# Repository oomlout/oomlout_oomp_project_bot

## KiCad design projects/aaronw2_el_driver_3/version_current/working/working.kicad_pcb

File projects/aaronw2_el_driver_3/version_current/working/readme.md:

# OOMP Project  
##   by   
  
oomp key:   
(snippet of original readme)  
  
- el-driver-3  
EL Wire Driver using Microchip MIC4832  
  
Copyright (C) 2021 Aaron Williams  
  
The enable pin is active high and requires 3V up to VCC.  It is pulled  
low by a 1M resistor.  This board is optimized for 100Hz and 3 square inches  
of EL panel.  
  
VCC is 3-5V  
  
Note that C2 must be rated for 250VDC or higher.  
  
See page 11 of the MIC4832 datasheet at:  
https://ww1.microchip.com/downloads/en/DeviceDoc/MIC4832-Low-Noise-220VPP-EL-Driver-DS20006163A.pdf  
  
  full source readme at [readme_src.md](readme_src.md)  
  
source repo at:   
## Board  

## Schematic  

[schematic pdf](working_schematic.pdf)  
## Images

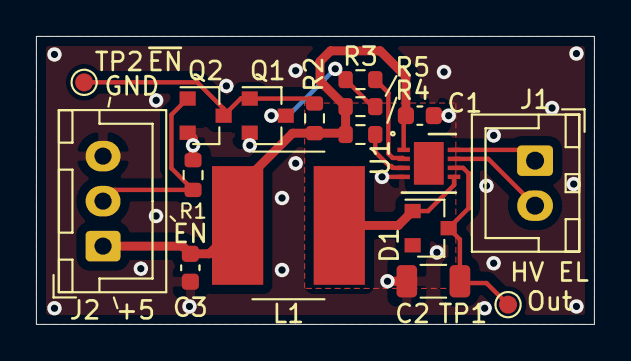
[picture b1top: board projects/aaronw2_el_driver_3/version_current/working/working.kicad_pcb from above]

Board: 2 copper layers, 31.0 x 16.0 mm, 17 parts (0 on the bottom side), 11 nets.

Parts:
C1: 2.2uF; C_0603_1608Metric
C2: 0.015uF 250V; C_1206_3216Metric
C3: 10uF; C_0603_1608Metric
D1: BAS20; SOT-23
J1: Conn_01x02; JST_XH_B2B-XH-A_1x02_P2.50mm_Vertical
J2: Conn_01x03; JST_XH_B3B-XH-A_1x03_P2.50mm_Vertical
L1: 220uH; L_Bourns_SRN8040TA
Q1, Q2: BSS138; SOT-23
R1, R2: 1M; R_0603_1608Metric
R3: 309K; R_0603_1608Metric
R4: 1.69M; R_0603_1608Metric
R5: 1K; R_0603_1608Metric
TP1: TestPoint_Small; TestPoint_Pad_D1.0mm
TP2: TestPoint; TestPoint_Pad_D1.0mm
U1: MIC4832; DFN-8-1EP_3x3mm_P0.5mm_EP1.66x2.38mm

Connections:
+5V: C1.1, C3.1, J2.1, L1.1, R2.2, R4.2, R5.2, U1.1
/CS: C2.1, D1.3, TP1.1, U1.6
/EK_VB: J1.2, U1.7
/EL_VA: J1.1, U1.8
/EN: J2.2, Q2.1, R1.2
/SW: D1.1, L1.2, U1.5
/~EN: Q1.1, Q2.3, R2.1, TP2.1
GND: C1.2, C2.2, C3.2, J2.3, Q1.2, Q2.2, R1.1, U1.4
unnamed: Q1.3, R3.2, R5.1
unnamed: R3.1, U1.2
unnamed: R4.1, U1.3

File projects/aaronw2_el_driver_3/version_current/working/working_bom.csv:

"Id";"Designator";"Footprint";"Quantity";"Designation";"Supplier and ref";
1;"C3";"C_0603_1608Metric";1;"10uF";;;
2;"R5";"R_0603_1608Metric";1;"1K";;;
3;"R2,R1";"R_0603_1608Metric";2;"1M";;;
4;"Q2,Q1";"SOT-23";2;"BSS138";;;
5;"U1";"DFN-8-1EP_3x3mm_P0.5mm_EP1.66x2.38mm";1;"MIC4832";;;
6;"R4";"R_0603_1608Metric";1;"1.69M";;;
7;"R3";"R_0603_1608Metric";1;"309K";;;
8;"L1";"L_Bourns_SRN8040TA";1;"220uH";;;
9;"J2";"JST_XH_B3B-XH-A_1x03_P2.50mm_Vertical";1;"Conn_01x03";;;
10;"J1";"JST_XH_B2B-XH-A_1x02_P2.50mm_Vertical";1;"Conn_01x02";;;
11;"D1";"SOT-23";1;"BAS20";;;
12;"C2";"C_1206_3216Metric";1;"0.015uF 250V";;;
13;"C1";"C_0603_1608Metric";1;"2.2uF";;;

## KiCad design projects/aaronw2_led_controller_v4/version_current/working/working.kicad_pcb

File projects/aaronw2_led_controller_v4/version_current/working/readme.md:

# OOMP Project  
##   by   
  
oomp key:   
(snippet of original readme)  

  full source readme at [readme_src.md](readme_src.md)  
  
source repo at:   
## Board  

## Schematic  

[schematic pdf](working_schematic.pdf)  
## Images

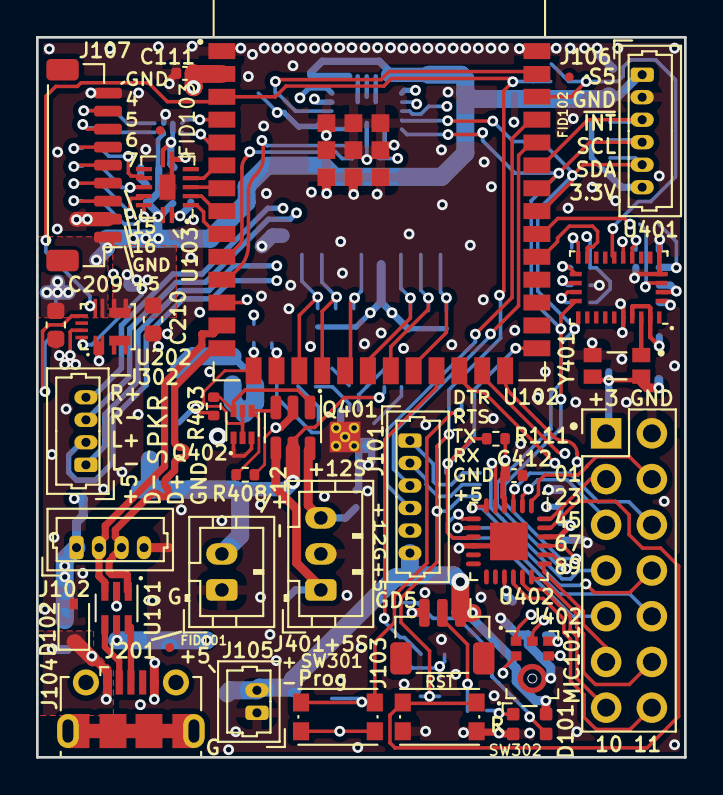
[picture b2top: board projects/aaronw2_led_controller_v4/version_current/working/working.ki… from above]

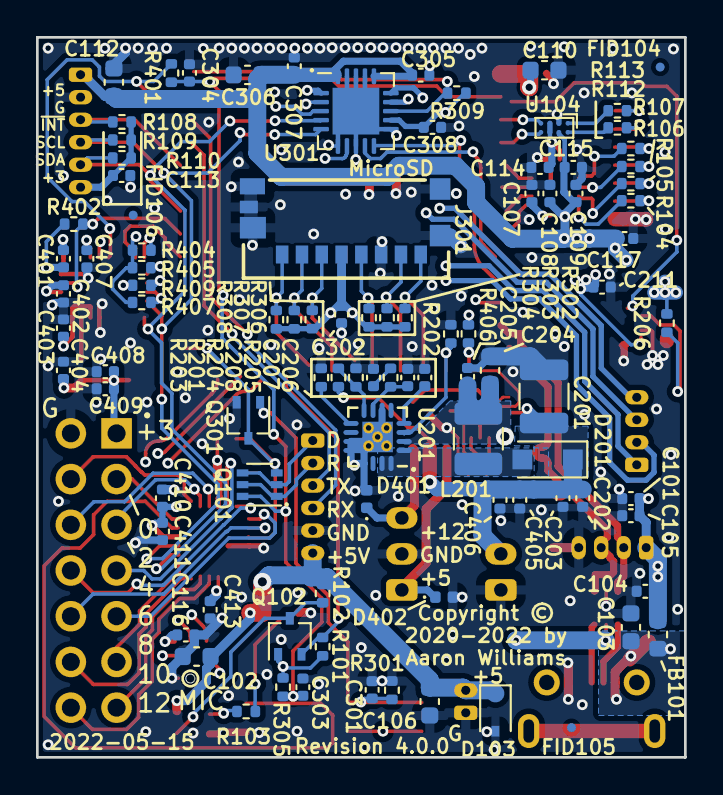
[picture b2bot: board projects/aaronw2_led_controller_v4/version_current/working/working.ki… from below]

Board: 4 copper layers, 36.0 x 40.0 mm, 130 parts (95 on the bottom side), 92 nets.

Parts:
C101, C105, C109, C113, C114, C115, C117, C202, C211, C302, C303, C401, C405, C408, C410: 1uF; C_0402_1005Metric
C102, C103, C106, C112, C306: 10uF; C_0603_1608Metric
C104, C107, C108, C111, C116, C203, C205, C301, C304, C305, C307, C308, C402, C403, C404, C406, C407, C409, C411, C412, C413: 0.1uF; C_0402_1005Metric
C110, C204, C209, C210: 22uF; C_0603_1608Metric
C201: 47uF; C_1210_3225Metric
C206: 22nF; C_0402_1005Metric
C207: 1.5nF; C_0402_1005Metric
C208: 33nF; C_0402_1005Metric
D101: WS2812_2020; LED_WS2812_2020
D102, D103: UDD32C12L01; D_SOD-323
D201: SMD34PL-TP; D_SOD-123F
D401, D402: CDBQR0230R-HF; D_0402_1005Metric
FB101: 2A 300 ohm@100MHz; L_0603_1608Metric
FID101, FID102, FID103, FID104, FID105, FID106: Fiducial; Fiducial_0.5mm_Mask1mm
J101, J106: Molex PicoBlade 6-pin; Molex_PicoBlade_53047-0610_1x06_P1.25mm_Vertical
J102, J302: Molex PicoBlade 4-pin; Molex_PicoBlade_53047-0410_1x04_P1.25mm_Vertical
J103: STATUS OUT; JST_SH_BM03B-SRSS-TB_1x03-1MP_P1.00mm_Vertical
J104: USB_B_Micro; USB_Micro-B_Molex-105017-0001
J105: POWER IN; Molex_PicoBlade_53047-0210_1x02_P1.25mm_Vertical
J107: 5V_LOGIC; JST_SH_BM09B-SRSS-TB_1x09-1MP_P1.00mm_Vertical
J201: 12V_OUT; JST_PH_B2B-PH-K_1x02_P2.00mm_Vertical
J301: Micro_SD_Card; microSD_HC_Molex_047571-0001
J401: Fan PWM; JST_PH_B3B-PH-K_1x03_P2.00mm_Vertical
J402: GPIO_CONN; PinHeader_2x07_P2.54mm_Vertical
L201: 2.2uH; L_1210_3225Metric
MIC101: SPH0645LM4H-B; Knowles_LGA-6_3.5x2.65mm
Q101: UMH3N; SOT-363_SC-70-6
Q102, Q301: BSS138; SOT-323_SC-70
Q401: SIL2301-TP; SOT-23-6
Q402: EM6K7T2R; SOT-563
R101, R102, R108, R404, R405: 4.7K; R_0402_1005Metric
R103, R104, R105, R106, R107, R112, R113: 33; R_0402_1005Metric
R109, R110: 2.2K; R_0402_1005Metric
R111, R202, R204, R206, R301, R302, R303, R304, R305, R306, R307, R308, R309, R401, R402, R403, R406, R407, R408, R409: 10K; R_0402_1005Metric
R201: 86.6K; R_0402_1005Metric
R203: 18.7K; R_0402_1005Metric
R205: 1.54K; R_0402_1005Metric
SW301, SW302: KMR2; SW_Push_1P1T_NO_CK_KMR2
U101: USBUF02W6; SOT-323-6L
U102: ESP32-S3-WROOM-2-N32R8V
U103: NTS0104BQ,115; SOT-762-1
U104: TCA9406ZYPR; Texas_DSBGA-8_0.9x1.9mm_Layout2x4_P0.5mm
U201: TPS55340-Q1; QFN-16-1EP_3x3mm_P0.5mm_EP2.7x2.7mm_ThermalVias
U202: MPM3810GQB-33; Monolithic_QFN-12-2.5x3.0mm_P0.4mm
U301: SSM2518CPZ; LFCSP-20-1EP_4x4mm_P0.5mm_EP2.6x2.6mm
U401: BNO085; LGA-28_5.2x3.8mm_P0.5mm
U402: PCA9575HF; HWQFN-24_EP_4x4_Pitch0.5mm
Y401: OM-7604-C7; OSC_OM-7604-C7

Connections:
+3V3: C107.1, C110.1, C111.1, C113.1, C114.1, C116.1, C210.1, C211.1, C302.1, C308.1, C401.1, C402.1, C403.1, C404.1, C408.1, C409.1, C410.1, C411.1, C412.1, C413.1, J106.6, J301.4 (VDD), J402.1, MIC101.2 (SEL), MIC101.5 (VDD), Q102.1 (G), R101.2, R108.2, R109.2, R110.2, R111.2, R302.2, R303.2, R304.2, R305.1, R306.2, R307.2, R308.2, R309.1, R402.1, R404.2, R405.2, R406.1, R407.1, SW301.1, U101.5 (V3.3), U102.2 (3V3), U103.1 (VCCA), U103.8 (OE), U104.C1 (VCCA), U104.C2 (OE), U202.12 (OUT_S), U202.56 (OUT), U301.3 (ADDR), U301.12 (DVDD), U401.3 (VDD), U401.10 (BL_IND), U401.26 (XOUT32), U401.28 (VDDIO), U402.4 (VDD(IO0)), U402.15 (VDD(IO1)), U402.22 (VDD), Y401.3 (CLKOE), Y401.4 (VDD)
+5V: C101.1, C102.1, C104.1, C105.1, C106.1, C108.1, C109.1, C112.1, C115.1, C117.1, C204.1, C205.1, C209.1, C305.1, C306.1, C307.1, D101.4 (VDD), D103.1 (K), FB101.2, J101.6, J102.1, J103.1, J105.2, J106.1, J107.1, L201.1, Q401.2 (S), R102.2, R206.2, R408.1, U103.14 (VCCB), U104.B2 (VCCB), U201.2 (VIN), U202.7 (VIN), U301.16 (PVDD), U301.20 (PVDD)
+12V: C201.1, C202.1, C203.1, C405.1, C406.1, D201.1 (K), J201.2, Q401.5 (S), R201.1, R403.1
/D+: J104.3 (D+), U101.6 (D4)
/D-: J104.2 (D-), U101.4 (D3)
/DTR: J101.1, Q101.2 (B1), Q101.4 (E2)
/I2S0_BCLK: MIC101.4 (BCLK), U102.26 (STR_3.3_1.8/IO45)
/I2S0_DIN: MIC101.6 (DATA_OUT), U102.25 (IO48)
/I2S0_WSEL: MIC101.1 (WS), U102.24 (IO47)
/IO4: U102.4 (IO4), U104.D1 (SDA_A)
/IO4_H: J107.8, R113.1
/IO5: U102.5 (IO5), U104.D2 (SCL_A)
/IO5_H: J107.7, R112.1
/IO6: U102.6 (IO6), U103.5 (A4)
/IO6_H: J107.6, R107.1
/IO7: U102.7 (IO7), U103.4 (A3)
/IO7_H: J107.5, R106.1
/IO15: U102.8 (IO15), U103.3 (A2)
/IO15_H: J107.4, R105.1
/IO16_H: J107.3, R104.1
/Motion and GPIO/CAP: C407.1, U401.9 (CAP)
/Motion and GPIO/COM2: R407.2, U401.18 (COM2)
/Motion and GPIO/COM3: R409.1, U401.17 (COM3)
/Motion and GPIO/H_SCL: R404.1, U401.15 (H_SCL)
/Motion and GPIO/H_SDA: R405.1, U401.16 (H_SDA)
/Motion and GPIO/P0_0: J402.3, U402.24 (P0_0)
/Motion and GPIO/P0_1: J402.4, U402.1 (P0_1)
/Motion and GPIO/P0_2: J402.5, U402.2 (P0_2)
/Motion and GPIO/P0_3: J402.6, U402.3 (P0_3)
/Motion and GPIO/P0_4: J402.7, U402.5 (P0_4)
/Motion and GPIO/P0_5: J402.8, U402.6 (P0_5)
/Motion and GPIO/P0_6: J402.9, U402.7 (P0_6)
/Motion and GPIO/P0_7: J402.10, U402.8 (P0_7)
/Motion and GPIO/P1_0: J402.11, U402.19 (P1_0)
/Motion and GPIO/P1_1: J402.12, U402.18 (P1_1)
/Motion and GPIO/P1_2: J402.13, U402.17 (P1_2)
/Motion and GPIO/P1_3: J402.14, U402.16 (P1_3)
/Motion and GPIO/SW_5V_IO1: D402.1 (K), J401.1, Q401.4 (D)
/Motion and GPIO/SW_12V: D401.1 (K), J401.3, Q401.6 (D)
/Motion and GPIO/XIN32: U401.27 (XIN32), Y401.1 (CLKOUT)
/Motion and GPIO/~EN_5V: Q401.3 (G), Q402.4 (D), R408.2
/Motion and GPIO/~EN_12V: Q401.1 (G), Q402.6 (D), R403.2
/Power Supplies/COMP: C207.1, R205.2, U201.7 (COMP)
/Power Supplies/EN_5V: R206.1, U202.9 (EN)
/Power Supplies/FB: R201.2, R204.1, U201.8 (FB)
/Power Supplies/FREQ: R203.1, U201.9 (FREQ)
/Power Supplies/SS: C206.1, U201.4 (SS)
/Power Supplies/SW: D201.2 (A), L201.2, U201.1 (SW), U201.15 (SW), U201.16 (SW)
/RTS: J101.2, Q101.1 (E1), Q101.5 (B2)
/RXD0: J101.4, U102.37 (TXD0)
/Reset, Boot, Amp, and SD Card/PGM_IO0_DRV: C301.1, Q301.1 (G), R301.2, SW301.2
/Reset, Boot, Amp, and SD Card/SPKR_L+: J302.2, U301.1 (OUTL+)
/Reset, Boot, Amp, and SD Card/SPKR_L-: J302.1, U301.2 (OUTL-)
/Reset, Boot, Amp, and SD Card/SPKR_R+: J302.4, U301.15 (OUTR+)
/Reset, Boot, Amp, and SD Card/SPKR_R-: J302.3, U301.14 (OUTR-)
/STATUS_LED: Q102.2 (S), R101.1, U102.23 (IO21)
/STS_5V: D101.3 (DIN), Q102.3 (D), R102.1
/STS_DO: J103.2, R103.1
/TXD0: J101.3, U102.36 (RXD0)
/USB_DN: J102.2, U101.3 (D2), U102.13 (USB_DN/IO19)
/USB_DP: J102.3, U101.1 (D1), U102.14 (USB_DP/IO20)
AMP_PWR: R309.2, U102.39 (IO1), U301.13 (~SD)
EN_12V: R202.2, U102.16 (STR_ROM_BOOT/IO46), U201.3 (EN)
FAN_PWM: Q402.2 (G), Q402.5 (G), R406.2, U102.15 (IO3/STR_JTAG_USB)
GND: C101.2, C102.2, C103.2, C104.2, C105.2, C106.2, C107.2, C108.2, C109.2, C110.2, C111.2, C112.2, C113.2, C114.2, C115.2, C116.2, C117.2, C201.2, C202.2, C203.2, C204.2, C205.2, C206.2, C207.2, C208.2, C209.2, C210.2, C211.2, C301.2, C302.2, C303.2, C304.2, C305.2, C306.2, C307.2, C308.2, C401.2, C402.2, C403.2, C404.2, C405.2, C406.2, C407.2, C408.2, C409.2, C410.2, C411.2, C412.2, C413.2, D101.2 (VSS), D102.2 (A), D103.2 (A), D401.2 (A), D402.2 (A), J101.5, J102.4, J103.3, J104.5 (GND), J105.1, J106.2, J107.2, J107.9, J201.1, J301.6 (VSS), J301.9 (SHIELD), J401.2, J402.2, MIC101.3 (GND), Q301.2 (S), Q402.1 (S), Q402.3 (S), R202.1, R203.2, R204.2, R301.1, R409.2, SW302.1, U101.2 (GND), U102.1 (GND), U102.40 (GND), U102.41 (GND), U103.7 (GND), U103.15 (GND), U104.B1 (GND), U201.6 (AGND), U201.11 (PGND), U201.12 (PGND), U201.13 (PGND), U201.17 (AGND), U202.1 (PGND), U202.2 (PGND), U202.11 (AGND), U301.6 (MCLK), U301.8 (GND), U301.11 (SAMOD), U301.17 (GND), U301.18 (GND), U301.19 (GND), U301.21 (GND), U401.2 (GND), U401.5 (PS1), U401.6 (PS0), U401.25 (GNDIO), U402.10 (GND), U402.25 (GND), Y401.2 (GND)
I2S1_BCLK: U102.12 (IO8), U301.7 (BCLK)
I2S1_DOUT: U102.11 (IO18), U301.10 (SDATA)
I2S1_WSEL: U102.10 (IO17), U301.9 (LRCLK)
IO16: U102.9 (IO16), U103.2 (A1)
unnamed: C208.1, R205.1
unnamed: D101.1 (DOUT), R103.2
unnamed: R104.2, U103.13 (B1)
unnamed: R105.2, U103.12 (B2)
unnamed: R106.2, U103.11 (B3)
unnamed: R107.2, U103.10 (B4)
unnamed: R112.2, U104.A2 (SCL_B)
unnamed: R113.2, U104.A1 (SDA_B)
SCL: J106.4, R109.1, U102.34 (IO41), U301.5 (SCL), U401.19 (COM1), U402.21 (SCL)
SDA: J106.5, R110.1, U102.33 (IO40), U301.4 (SDA), U401.20 (COM0), U402.20 (SDA)
SD_CLK: J301.5 (CLK), R304.1, U102.19 (IO11)
SD_CMD: J301.3 (CMD), R306.1, U102.20 (IO12)
SD_D0: J301.7 (DAT0), R303.1, U102.18 (IO10)
SD_D1: J301.8 (DAT1), R302.1, U102.17 (IO9)
SD_D2: J301.1 (DAT2), R308.1, U102.22 (IO14)
SD_D3: J301.2 (DAT3/CD), R307.1, U102.21 (IO13)
VBUS: C103.1, D102.1 (K), FB101.1, J104.1 (VBUS)
~INT2: U102.31 (IO38), U401.14 (~INT)
~INT3: J106.3, R108.1, U102.35 (IO42)
~INT: Q101.3 (C2), Q301.3 (D), R111.1, U102.27 (IO0/STR_SPI_DNLD), U402.9 (~INT)
~M_BOOT_LOAD: R402.2, U102.32 (IO39), U401.4 (~BOOT_LOAD_PIN)
~RESET: C303.1, C304.1, Q101.6 (C1), R305.2, R401.1, SW302.2, U102.3 (EN), U202.8 (PG), U402.23 (~RESET)
~RST_BNO085: R401.2, U102.38 (IO2), U401.11 (~RESET)

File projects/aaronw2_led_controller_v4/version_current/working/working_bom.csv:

"Id";"Designator";"Footprint";"Quantity";"Designation";"Supplier and ref";
1;"FID103,FID101,FID102,FID104,FID106,FID105";"Fiducial_0.5mm_Mask1mm";6;"Fiducial";;;
2;"U401";"LGA-28_5.2x3.8mm_P0.5mm";1;"BNO085";;;
3;"J104";"USB_Micro-B_Molex-105017-0001";1;"USB_B_Micro";;;
4;"C111,C412,C205,C403,C308,C409,C305,C301,C108,C402,C406,C304,C116,C411,C203,C407,C404,C413,C307,C107,C104";"C_0402_1005Metric";21;"0.1uF";;;
5;"U101";"SOT-323-6L";1;"USBUF02W6";;;
6;"D102,D103";"D_SOD-323";2;"UDD32C12L01";;;
7;"U402";"HWQFN-24_EP_4x4_Pitch0.5mm";1;"PCA9575HF";;;
8;"SW302,SW301";"SW_Push_1P1T_NO_CK_KMR2";2;"KMR2";;;
9;"J101,J106";"Molex_PicoBlade_53047-0610_1x06_P1.25mm_Vertical";2;"Molex PicoBlade 6-pin";;;
10;"J107";"JST_SH_BM09B-SRSS-TB_1x09-1MP_P1.00mm_Vertical";1;"5V_LOGIC";;;
11;"R408,R111,R403,R307,R305,R202,R206,R409,R401,R301,R308,R407,R303,R402,R302,R204,R406,R304,R306,R309";"R_0402_1005Metric";20;"10K";;;
12;"MIC101";"Knowles_LGA-6_3.5x2.65mm";1;"SPH0645LM4H-B";;;
13;"J105";"Molex_PicoBlade_53047-0210_1x02_P1.25mm_Vertical";1;"POWER IN";;;
14;"J402";"PinHeader_2x07_P2.54mm_Vertical";1;"GPIO_CONN";;;
15;"Q402";"SOT-563";1;"EM6K7T2R";;;
16;"U102";"ESP32-S3-WROOM-2-N32R8V";1;"ESP32-S3-WROOM-2-N32R8V";;;
17;"U202";"Monolithic_QFN-12-2.5x3.0mm_P0.4mm";1;"MPM3810GQB-33";;;
18;"J103";"JST_SH_BM03B-SRSS-TB_1x03-1MP_P1.00mm_Vertical";1;"STATUS OUT";;;
19;"Q401";"SOT-23-6";1;"SIL2301-TP";;;
20;"C210,C209,C204,C110";"C_0603_1608Metric";4;"22uF";;;
21;"J201";"JST_PH_B2B-PH-K_1x02_P2.00mm_Vertical";1;"12V_OUT";;;
22;"J102,J302";"Molex_PicoBlade_53047-0410_1x04_P1.25mm_Vertical";2;"Molex PicoBlade 4-pin";;;
23;"U103";"SOT-762-1";1;"NTS0104BQ,115";;;
24;"D101";"LED_WS2812_2020";1;"WS2812_2020";;;
25;"J401";"JST_PH_B3B-PH-K_1x03_P2.00mm_Vertical";1;"Fan PWM";;;
26;"Y401";"OSC_OM-7604-C7";1;"OM-7604-C7";;;
27;"C103,C102,C306,C112,C106";"C_0603_1608Metric";5;"10uF";;;
28;"C207";"C_0402_1005Metric";1;"1.5nF";;;
29;"C408,C302,C113,C410,C114,C401,C117,C115,C105,C303,C405,C211,C101,C202,C109";"C_0402_1005Metric";15;"1uF";;;
30;"R103,R113,R112,R107,R106,R104,R105";"R_0402_1005Metric";7;"33";;;
31;"D201";"D_SOD-123F";1;"SMD34PL-TP";;;
32;"R405,R102,R101,R404,R108";"R_0402_1005Metric";5;"4.7K";;;
33;"D402,D401";"D_0402_1005Metric";2;"CDBQR0230R-HF";;;
34;"R109,R110";"R_0402_1005Metric";2;"2.2K";;;
35;"R203";"R_0402_1005Metric";1;"18.7K";;;
36;"C206";"C_0402_1005Metric";1;"22nF";;;
37;"U104";"Texas_DSBGA-8_0.9x1.9mm_Layout2x4_P0.5mm";1;"TCA9406ZYPR";;;
38;"U201";"QFN-16-1EP_3x3mm_P0.5mm_EP2.7x2.7mm_ThermalVias";1;"TPS55340-Q1";;;
39;"Q301,Q102";"SOT-323_SC-70";2;"BSS138";;;
40;"C201";"C_1210_3225Metric";1;"47uF";;;
41;"Q101";"SOT-363_SC-70-6";1;"UMH3N";;;
42;"C208";"C_0402_1005Metric";1;"33nF";;;
43;"R205";"R_0402_1005Metric";1;"1.54K";;;
44;"R201";"R_0402_1005Metric";1;"86.6K";;;
45;"J301";"microSD_HC_Molex_047571-0001";1;"Micro_SD_Card";;;
46;"L201";"L_1210_3225Metric";1;"2.2uH";;;
47;"U301";"LFCSP-20-1EP_4x4mm_P0.5mm_EP2.6x2.6mm";1;"SSM2518CPZ";;;
48;"FB101";"L_0603_1608Metric";1;"2A 300 ohm@100MHz";;;

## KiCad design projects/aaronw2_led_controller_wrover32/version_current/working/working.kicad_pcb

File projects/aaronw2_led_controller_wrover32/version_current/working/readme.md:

# OOMP Project  
##   by   
  
oomp key:   
(snippet of original readme)  
  
- led-controller-wrover32  
Wrover32 based LED controller for NeoPixels and DotStars with 5v signalling  
and micro SD  
  
Power:  
  
This board is powered by 5V and generates a 3.3V supply via U1.  This board  
may draw up to 500ma of current at 5V.  The 3.3V supply is capable of  
generating up to 1A.  
  
This board makes use of a Torex Semiconductor XCL220 micro DC/DC converter  
to efficiently provide 3.3v of power.  This inexpensive device is reportedly  
93% efficient which should increase battery life and reduce heat buildup.  
  
Do not draw more than 500ma from any single power or ground pin on J2 or J4.  
  
On J5, VBUS is 5V as are pins 9 and 12 on J4 and pin 1 on J2.  
J6 and J7 also provide +5V at the + terminal.  
  
5V may be shunted through the board, but limit the current to no more than 2A.  
  
5V may be supplied by any pin, however power provided by the micro SD  
connector J3 should be limited to 500 ma.  
  
USB:  
  
There are two USB connectors on the board for programming.  The Micro USB  
connector J3 or J5 may be used.  Do not use both connectors.  J5 is designed  
so either a 4 pin header or a USB cable can be soldered to the board,  
eliminating the need to use micro USB.  
  
The USB port is connected to a SI Labs CP2102 USB to serial UART for  
programming and debugging purposes.  
  
I/O:  
  
Unlike most if not all other ESP32 based boards, this board includes a  
3V to 5V bidirectional level shifter for IO25, IO26, IO32 and IO33.  These  
I/O ports can also be driven by the RTC in the ESP32 to help offload driving  
  full source readme at [readme_src.md](readme_src.md)  
  
source repo at:   
## Board  

## Schematic  

[schematic pdf](working_schematic.pdf)  
## Images

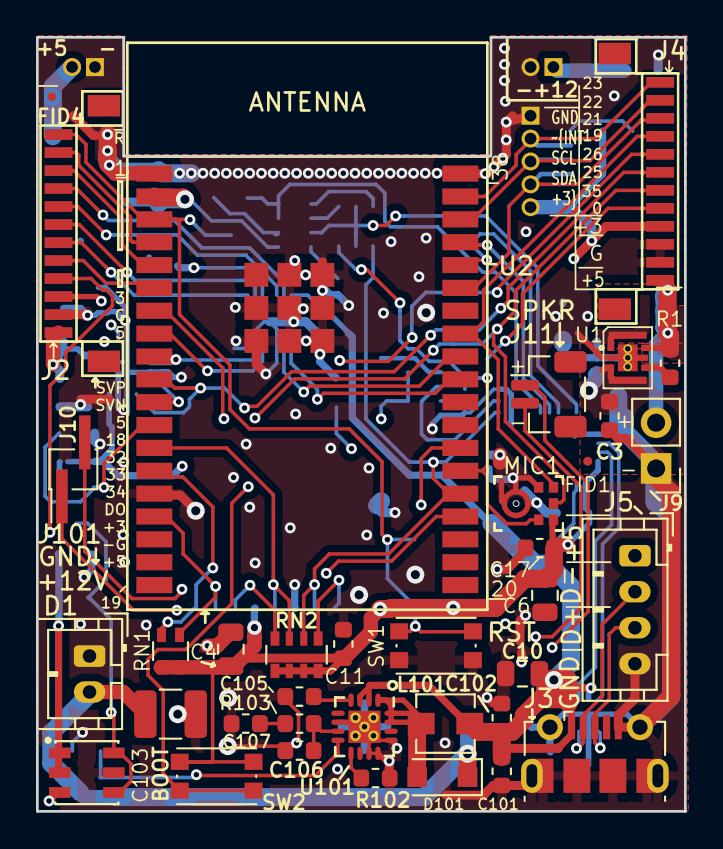
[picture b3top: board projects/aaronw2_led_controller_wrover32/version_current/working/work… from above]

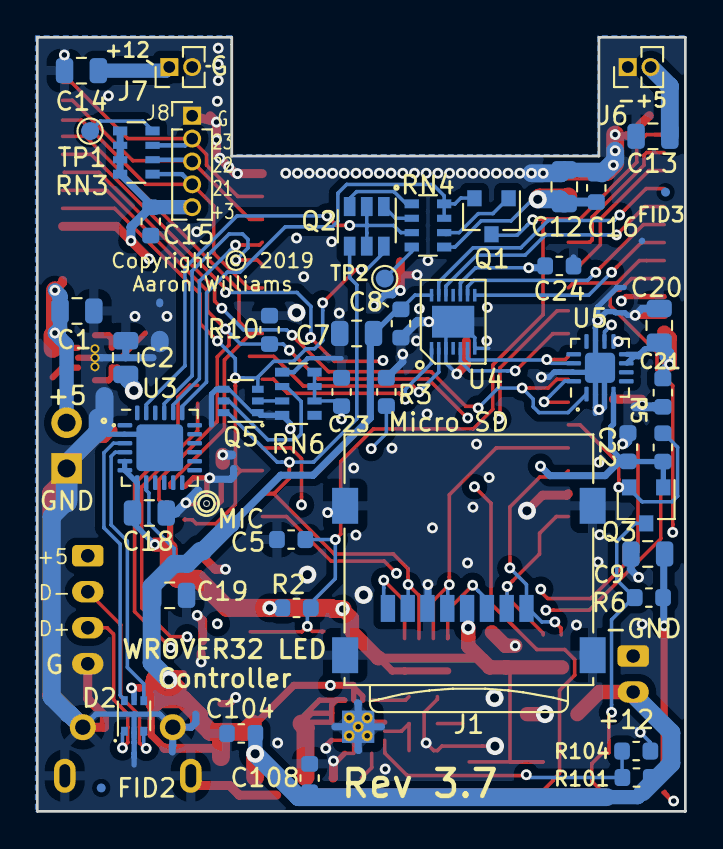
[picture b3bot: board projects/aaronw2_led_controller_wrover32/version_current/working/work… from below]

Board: 4 copper layers, 36.0 x 43.0 mm, 82 parts (46 on the bottom side), 59 nets.

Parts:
C1, C2, C4, C6, C7, C9, C10, C13, C14, C18, C19, C20: 10uF; C_0805_2012Metric
C3, C11, C15, C104: 1uF; C_0603_1608Metric
C5, C8, C16, C17, C21, C22, C24, C102, C108: 0.1uF; C_0603_1608Metric
C12: 22uF; C_0805_2012Metric
C23, C105: 22nF; C_0603_1608Metric
C101: 22uF; C_0603_1608Metric
C103: 47uF; C_1210_3225Metric
C106: 820pF; C_0603_1608Metric
C107: 47nF; C_0603_1608Metric
D1: WS2813-MINI; LED_WS2813-MINI-2
D2: USBLC6-2P6; SOT-666
D101: D_Schottky; D_SOD-123F
FID1, FID2, FID3, FID4: DNF; Fiducial_0.5mm_Mask1mm
J1: Micro_SD_Card; microSD_HC_Wuerth_693072010801
J2, J4: BM12B-SRSS-TBT(LF)(SN); BM12B-SRSS-TB
J3: USB_B_Micro; USB_Micro-B_Molex-105017-0001
J5: Conn_01x04; JST_PH_B4B-PH-K_1x04_P2.00mm_Vertical
J6, J7: Conn_01x02 DNF; PinHeader_1x02_P1.27mm_Vertical
J8: Conn_01x05 DNF; PinHeader_1x05_P1.27mm_Vertical
J9: Conn_01x02 DNF; PinHeader_1x02_P2.54mm_Vertical
J10: Conn_01x02 DNF; PinHeader_1x02_P1.27mm_Vertical_SMD_Pin1Left
J11: Conn_01x02; JST_SH_BM02B-SRSS-TB_1x02-1MP_P1.00mm_Vertical
J101: Conn_01x02; JST_PH_B2B-PH-K_1x02_P2.00mm_Vertical
L101: 3.3uH; L_Vishay_IHLP-1212
MIC1: SPH0645LM4H-B
Q1: MMSS8050-H-TP; SOT-23
Q2: FMB2222A; SOT-23-6
Q3: BSS138; SOT-23
Q5: BSS138DW-7-F; SOT-363_SC-70-6
R1, R3, R104: 10K; R_0603_1608Metric
R2: 470; R_0603_1608Metric
R5, R6: 4.7K; R_0603_1608Metric
R10: 100K; R_0603_1608Metric
R101: 86.6K; R_0603_1608Metric
R102: 18.7K; R_0603_1608Metric
R103: 1.62K; R_0603_1608Metric
RN1: 10K; R_Array_Convex_2x0603
RN2: 10K; R_Array_Convex_4x0603
RN3: 4.7K; R_Array_Convex_4x0603
RN4, RN6: 100K; R_Array_Convex_4x0603
SW1, SW2: SW_SPST_KMR2
TP1, TP2: DNF; TestPoint_Pad_D1.0mm
U1: XCL220; CL-2025-02
U2: ESP32-WROVER; ESP32-WROOVER
U3: CP2104; QFN-24-1EP_4x4mm_P0.5mm_EP2.6x2.6mm
U4: MAX3379EETD; TDFN-14_3x3mm_P0.4mm_EP1.78x2.35mm
U5: MAX98357A; VQFN-16-1EP_3x3mm_P0.5mm_EP1.68x1.68mm
U101: TPS55340-Q1; QFN-16-1EP_3x3mm_P0.5mm_EP2.7x2.7mm_ThermalVias

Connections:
+3V3: C2.1, C3.1, C4.1, C6.1, C11.1, C12.1, C15.1, C16.1, C17.1, C18.1, C22.1, C24.1, J1.4, J2.3, J4.9, J8.5, MIC1.5, Q3.1, R2.1, R5.2, RN1.1, RN1.2, RN2.1, RN2.2, RN2.3, RN2.4, RN3.5, RN3.6, RN3.7, RN3.8, RN4.5, SW2.1, U1.3, U1.8, U2.2, U3.5, U3.6, U3.7, U4.10, U5.4
+12V: C14.1, C103.1, C104.1, C108.1, D101.1, J7.1, J101.2, R101.1
/12v-booster/COMP: C106.1, R103.2, U101.7
/12v-booster/FB: R101.2, R104.1, U101.8
/12v-booster/FREQ: R102.1, U101.9
/12v-booster/SS: C105.1, U101.4
/12v-booster/SW: D101.2, L101.2, U101.1, U101.15, U101.16
/Amp/SPKR+: J10.1, J11.1, U5.9
/Amp/SPKR-: J10.2, J11.2, U5.10
/D+: D2.1, J3.3, J5.3
/D-: D2.3, J3.2, J5.2
/DO: D1.3, J2.4
/DTR: Q2.2, Q2.5, RN4.3, U3.23
/IO0_RTS_DRV: Q2.1, RN4.2
/IO2_RTS_DRV: Q2.3, RN4.1
/IO4: J1.8, RN2.5, U2.26
/IO12: J1.1, RN1.4, U2.14
/IO13: J1.2, RN1.3, U2.16
/IO14: J1.5, RN2.7, U2.13
/IO15: J1.3, RN2.8, U2.23
/IO19: J4.4, MIC1.1, U2.31
/IO21: J4.3, J8.4, RN3.1, U2.33
/IO22: J4.2, J8.3, RN3.2, U2.36
/IO23: J4.1, J8.2, RN3.3, U2.37
/IO27: Q3.2, R5.1, U2.12
/IO27_5V: D1.4, D1.6, Q3.3, R6.1
/IO34: J2.5, U2.6
/IO35: J4.7, MIC1.6, R10.2, U2.7
/RST_DTR_DRV: Q1.1, RN4.6
/RTS: Q1.2, RN4.7, RN4.8, U3.19
/RXD0: U2.34, U3.21
/Reset_Boot/PGM_IO0_DRV: Q5.5, RN6.6
/Reset_Boot/PGM_IO2_DRV: Q5.2, RN6.7
/Reset_Boot/~PGM_SW_OUT: C23.1, R3.1, RN6.2, RN6.3, RN6.4, SW2.2
/SENSOR_VN: J2.10, U2.5
/SENSOR_VP: J2.11, U2.4
/TXD0: U2.35, U3.20
/USB_D+: D2.6, U3.3
/USB_D-: D2.4, U3.4
GND: C1.2, C2.2, C3.2, C4.2, C5.2, C6.2, C7.2, C8.2, C9.2, C10.2, C11.2, C12.2, C13.2, C14.2, C15.2, C16.2, C17.2, C18.2, C19.2, C20.2, C21.2, C22.2, C23.2, C24.2, C101.2, C102.2, C103.2, C104.2, C105.2, C106.2, C107.2, C108.2, D1.5, D2.2, J1.6, J1.9, J2.2, J3.5, J3.6, J4.10, J4.11, J5.4, J6.1, J7.2, J8.1, J9.1, J101.1, MIC1.2, MIC1.3, Q5.1, Q5.4, R3.2, R10.1, R102.2, R104.2, RN6.5, RN6.8, SW1.1, U1.2, U1.5, U1.9, U2.1, U2.15, U2.38, U2.39, U3.2, U3.25, U4.3, U4.7, U4.15, U5.2, U5.3, U5.11, U5.15, U5.17, U101.6, U101.11, U101.12, U101.13, U101.17
IO0: J4.8, MIC1.4, Q2.6, Q5.3, U2.25
IO2: J1.7, Q2.4, Q5.6, RN2.6, U2.24
IO5: U2.29, U4.1
IO5_H: J2.9, U4.13
IO18: U2.30, U4.2
IO18_H: J2.8, U4.12
IO25: J4.6, U2.10, U5.1
IO26: J4.5, U2.11, U5.16
IO32: U2.8, U4.5
IO32_H: J2.7, U4.9
IO33: U2.9, U4.6, U5.14
IO33_H: J2.6, U4.8
unnamed: C107.1, R103.1
unnamed: R1.1, U1.4
unnamed: RN3.4, TP1.1
unnamed: RN4.4, TP2.1
unnamed: U1.1, U1.7
VBUS: C1.1, C7.1, C8.1, C9.1, C10.1, C13.1, C19.1, C20.1, C21.1, C101.1, C102.1, D1.1, D1.2, D2.5, J2.1, J3.1, J4.12, J5.1, J6.2, J9.2, L101.1, R1.2, R6.2, U1.6, U3.8, U4.14, U5.7, U5.8, U101.2, U101.3
~RESET: C5.1, J2.12, Q1.3, R2.2, SW1.2, U2.3

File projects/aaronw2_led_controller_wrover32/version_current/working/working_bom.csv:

"Id";"Designator";"Footprint";"Quantity";"Designation";"Supplier and ref";
1;"C18,C7,C20,C19,C6,C2,C9,C10,C13,C14,C1,C4";"C_0805_2012Metric";12;"10uF";;;
2;"U3";"QFN-24-1EP_4x4mm_P0.5mm_EP2.6x2.6mm";1;"CP2104";;;
3;"D1";"LED_WS2813-MINI-2";1;"WS2813-MINI";;;
4;"Q2";"SOT-23-6";1;"FMB2222A";;;
5;"U2";"ESP32-WROOVER";1;"ESP32-WROVER";;;
6;"U4";"TDFN-14_3x3mm_P0.4mm_EP1.78x2.35mm";1;"MAX3379EETD";;;
7;"C24,C8,C5,C22,C21,C108,C102,C17,C16";"C_0603_1608Metric";9;"0.1uF";;;
8;"J10";"PinHeader_1x02_P1.27mm_Vertical_SMD_Pin1Left";1;"Conn_01x02 DNF";;;
9;"J7,J6";"PinHeader_1x02_P1.27mm_Vertical";2;"Conn_01x02 DNF";;;
10;"MIC1";"SPH0645LM4H-B";1;"SPH0645LM4H-B";;;
11;"R3,R104,R1";"R_0603_1608Metric";3;"10K";;;
12;"SW1,SW2";"SW_SPST_KMR2";2;"SW_SPST_KMR2";;;
13;"Q5";"SOT-363_SC-70-6";1;"BSS138DW-7-F";;;
14;"U5";"VQFN-16-1EP_3x3mm_P0.5mm_EP1.68x1.68mm";1;"MAX98357A";;;
15;"Q1";"SOT-23";1;"MMSS8050-H-TP";;;
16;"R2";"R_0603_1608Metric";1;"470";;;
17;"RN6,RN4";"R_Array_Convex_4x0603";2;"100K";;;
18;"C23,C105";"C_0603_1608Metric";2;"22nF";;;
19;"J11";"JST_SH_BM02B-SRSS-TB_1x02-1MP_P1.00mm_Vertical";1;"Conn_01x02";;;
20;"FID4,FID3,FID2,FID1";"Fiducial_0.5mm_Mask1mm";4;"DNF";;;
21;"J9";"PinHeader_1x02_P2.54mm_Vertical";1;"Conn_01x02 DNF";;;
22;"J5";"JST_PH_B4B-PH-K_1x04_P2.00mm_Vertical";1;"Conn_01x04";;;
23;"J101";"JST_PH_B2B-PH-K_1x02_P2.00mm_Vertical";1;"Conn_01x02";;;
24;"J1";"microSD_HC_Wuerth_693072010801";1;"Micro_SD_Card";;;
25;"L101";"L_Vishay_IHLP-1212";1;"3.3uH";;;
26;"U101";"QFN-16-1EP_3x3mm_P0.5mm_EP2.7x2.7mm_ThermalVias";1;"TPS55340-Q1";;;
27;"C101";"C_0603_1608Metric";1;"22uF";;;
28;"C104,C15,C3,C11";"C_0603_1608Metric";4;"1uF";;;
29;"C106";"C_0603_1608Metric";1;"820pF";;;
30;"C107";"C_0603_1608Metric";1;"47nF";;;
31;"C103";"C_1210_3225Metric";1;"47uF";;;
32;"D101";"D_SOD-123F";1;"D_Schottky";;;
33;"R101";"R_0603_1608Metric";1;"86.6K";;;
34;"R102";"R_0603_1608Metric";1;"18.7K";;;
35;"R103";"R_0603_1608Metric";1;"1.62K";;;
36;"J8";"PinHeader_1x05_P1.27mm_Vertical";1;"Conn_01x05 DNF";;;
37;"RN3";"R_Array_Convex_4x0603";1;"4.7K";;;
38;"J3";"USB_Micro-B_Molex-105017-0001";1;"USB_B_Micro";;;
39;"Q3";"SOT-23";1;"BSS138";;;
40;"D2";"SOT-666";1;"USBLC6-2P6";;;
41;"J4,J2";"BM12B-SRSS-TB";2;"BM12B-SRSS-TBT(LF)(SN)";;;
42;"RN1";"R_Array_Convex_2x0603";1;"10K";;;
43;"RN2";"R_Array_Convex_4x0603";1;"10K";;;
44;"R5,R6";"R_0603_1608Metric";2;"4.7K";;;
45;"R10";"R_0603_1608Metric";1;"100K";;;
46;"C12";"C_0805_2012Metric";1;"22uF";;;
47;"U1";"CL-2025-02";1;"XCL220";;;

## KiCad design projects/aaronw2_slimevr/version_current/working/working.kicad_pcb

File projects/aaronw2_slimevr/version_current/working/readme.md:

# OOMP Project  
##   by   
  
(snippet of original readme)  

  full source readme at [readme_src.md](readme_src.md)  
  
source repo at:   
## Board  

## Schematic  

[schematic pdf](working_schematic.pdf)  
## Images

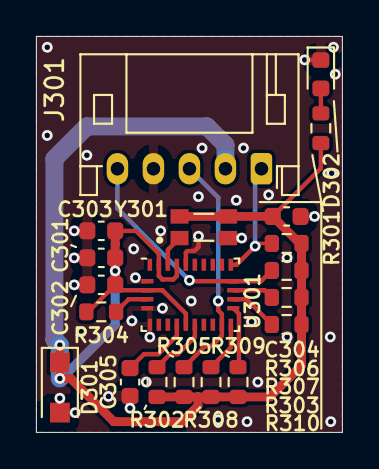
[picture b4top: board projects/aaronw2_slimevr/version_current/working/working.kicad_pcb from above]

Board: 2 copper layers, 17.0 x 22.0 mm, 20 parts (0 on the bottom side), 14 nets.

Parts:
C301: 10uF 10V; C_0603_1608Metric
C302, C303, C304, C305: 0.1uF; C_0603_1608Metric
D301: DSS12UTR; D_SOD-123F
D302: Green; LED_0603_1608Metric
J301: External Motion; JST_PH_S5B-PH-K_1x05_P2.00mm_Horizontal
R301: 330; R_0603_1608Metric
R302, R303, R304, R305, R310: 10K; R_0603_1608Metric
R306, R307, R308, R309: 2.2K; R_0603_1608Metric
U301: BNO085; LGA-28_5.2x3.8mm_P0.5mm
Y301: OM-7604-C7; OSC_OM-7604-C7

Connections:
+3V3: C301.1, C302.1, C303.1, C304.1, D301.1 (K), J301.2, R301.2, R302.1, R303.1, R304.1, R305.1, R306.1, R307.1, R308.1, R309.1, R310.1, U301.3 (VDD), U301.10 (BL_IND), U301.26 (XOUT32), U301.28 (VDDIO), Y301.3 (CLKOE), Y301.4 (VDD)
/B_CLK: U301.27 (XIN32), Y301.1 (CLKOUT)
/CAP: C305.1, U301.9 (CAP)
/SCL: J301.5, R307.2, U301.19 (COM1)
/SDA: J301.1, R306.2, U301.20 (COM0)
/~BNO_BOOT: R304.2, U301.4 (~BOOT_LOAD_PIN)
/~BNO_RESET: R302.2, U301.11 (~RESET)
/~INT1: J301.3, R305.2, U301.14 (INT)
GND: C301.2, C302.2, C303.2, C304.2, C305.2, D301.2 (A), D302.1 (K), J301.4, U301.2 (GND), U301.5 (PS1), U301.6 (PS0), U301.25 (GNDIO), Y301.2 (GND)
unnamed: D302.2 (A), R301.1
unnamed: R303.2, U301.18 (COM2)
unnamed: R308.2, U301.15 (H_SCL)
unnamed: R309.2, U301.16 (H_SDA)
unnamed: R310.2, U301.17 (COM3)

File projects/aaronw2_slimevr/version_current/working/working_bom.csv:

"Id";"Designator";"Footprint";"Quantity";"Designation";"Supplier and ref";
1;"R301";"R_0603_1608Metric";1;"330";;;
2;"C303,C304,C302,C305";"C_0603_1608Metric";4;"0.1uF";;;
3;"U301";"LGA-28_5.2x3.8mm_P0.5mm";1;"BNO085";;;
4;"J301";"JST_PH_S5B-PH-K_1x05_P2.00mm_Horizontal";1;"External Motion";;;
5;"R303,R304,R305,R302,R310";"R_0603_1608Metric";5;"10K";;;
6;"D302";"LED_0603_1608Metric";1;"Green";;;
7;"R306,R309,R307,R308";"R_0603_1608Metric";4;"2.2K";;;
8;"D301";"D_SOD-123F";1;"DSS12UTR";;;
9;"C301";"C_0603_1608Metric";1;"10uF 10V";;;
10;"Y301";"OSC_OM-7604-C7";1;"OM-7604-C7";;;

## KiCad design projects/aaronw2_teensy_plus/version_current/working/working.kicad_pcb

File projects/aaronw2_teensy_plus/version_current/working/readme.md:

# OOMP Project  
##   by   
  
oomp key:   
(snippet of original readme)  
  
Teensy Plus  
Revision 3.3  
  
Copyright (C) 2019 by Aaron Williams  
  
This board is designed to be mounted to a PJRC Teensy 4.0 and 3.2 board.  
It brings out the I/Os of the Teensy and provides a 3V to 5V level shifter  
and a WS2813mini NeoPixel in order to drive up to four channels of  
NeoPixels.  The 5V channels should be compatible with the FastLED library  
for the Teensy 4.0 (not 3.2).  In addition, this board provides a switchable  
12V, 500ma output for driving a fan or other 12V accessories.  Note that  
while the boost circuit is fairly efficient that it will draw around 2.75 times  
as much current at 5V as the 12V output, so at 500ma it could potentially  
draw around 1.4 amps.  If the 12V is not needed then it does not need to be  
stuffed.  
  
This board is designed to be mounted back-to-back with the Teensy 3.2 or  
4.0 board. Note that the extra pins on the back will not be accessible  
once this board is soldered in place.  It can be connected by soldering  
board headers or using headers and sockets.  
  
Not all of the pins are used and not all need to be hooked up.  
  
On/OFF, Program and VBat are not hooked up.  Additionally J9 does not  
need to be connected and can be used for an additional 5V pin.  
  
IO0, IO1, IO2 and IO3 are passed to the level shifter and IO23 is  
connected to the enable pin of the level shifter.  IO3 then goes to  
the WS2813mini.  
  
3.3V is obtained from the Teensy board which cannot supply a lot of  
current.  Please do not exceed 100ma.  
  
J8 brings provides 3.3V, ground and IO4   
  full source readme at [readme_src.md](readme_src.md)  
  
source repo at:   
## Board  

## Schematic  

[schematic pdf](working_schematic.pdf)  
## Images

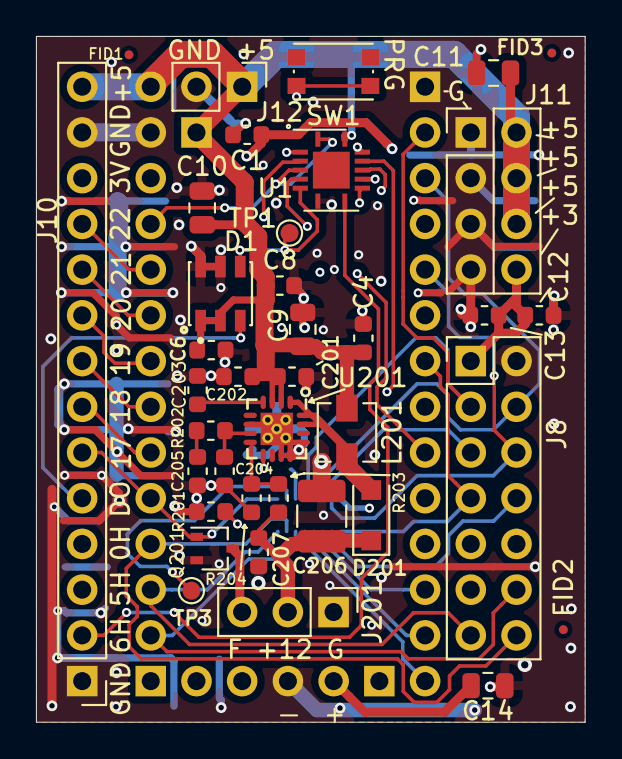
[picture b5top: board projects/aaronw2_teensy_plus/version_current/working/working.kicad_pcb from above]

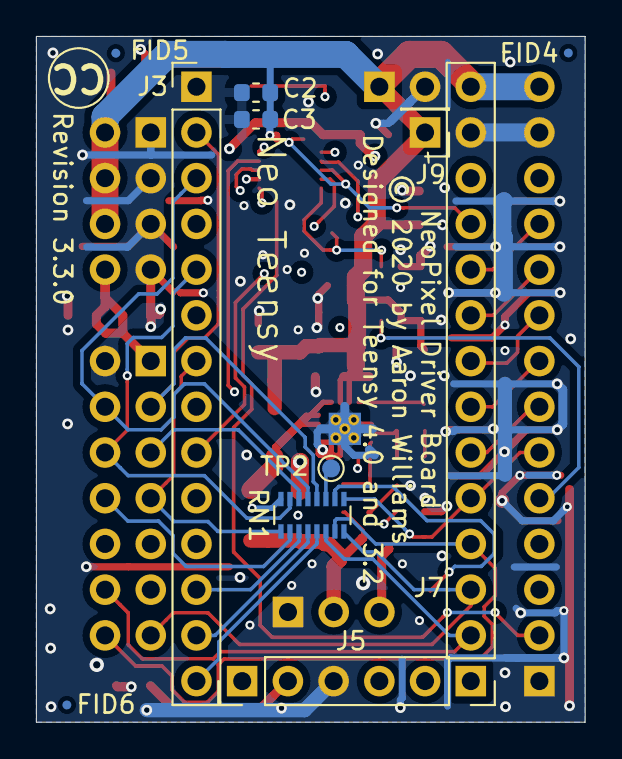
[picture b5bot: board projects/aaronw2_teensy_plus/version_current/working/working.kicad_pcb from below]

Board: 4 copper layers, 30.5 x 38.1 mm, 49 parts (11 on the bottom side), 42 nets.

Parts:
C1, C2, C4, C8, C13, C202: 0.1uF; C_0603_1608Metric
C3, C6, C12, C207: 1uF; C_0603_1608Metric
C9, C10, C11, C14: 10uF; C_0805_2012Metric
C201: 22uF; C_0603_1608Metric
C203: 22nF; C_0603_1608Metric
C204: 820pF; C_0603_1608Metric
C205: 47nF; C_0603_1608Metric
C206: 47uF; C_1210_3225Metric
D1: WS2813-MINI; LED_WS2813-MINI-2
D201: SS24FL; D_SOD-123F
FID1, FID2, FID3, FID4, FID5, FID6: FIDUCIAL_1MM; Fiducial_0.5mm_Mask1mm
J3, J7: Conn_01x14_Male; PinHeader_1x14_P2.54mm_Vertical
J5: Conn_01x05_Male; PinHeader_1x05_P2.54mm_Vertical
J8: Conn_02x07_Odd_Even; PinHeader_2x07_P2.54mm_Vertical
J9: Conn_01x01_Male; PinHeader_1x01_P2.54mm_Vertical
J10: Conn_01x14; PinHeader_1x14_P2.54mm_Vertical
J11: Conn_02x04_Odd_Even; PinHeader_2x04_P2.54mm_Vertical
J12: Conn_01x02; PinHeader_1x02_P2.54mm_Vertical
J201: Conn_01x03; PinHeader_1x03_P2.54mm_Vertical
L201: 3.3uH; L_Vishay_IHLP-1212
Q201: BSS214NW; SOT-323_SC-70
R201: 18.7K; R_0603_1608Metric
R202: 1.62k; R_0603_1608Metric
R203: 86.6k; R_0603_1608Metric
R204: 10k; R_0603_1608Metric
RN1: 100K; R_Array_Convex_8x0602
SW1: SW_SPST_KMR2
TP1, TP2, TP3: TestPoint; TestPoint_Pad_D1.0mm
U1: SN74AHCT125N; Texas_S-PVQFN-N14
U201: TPS55340-Q1; QFN-16-1EP_3x3mm_P0.5mm_EP2.7x2.7mm_ThermalVias

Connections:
+3V3: C1.1, C12.1, C13.1, C14.1, J5.2, J7.12, J8.1, J10.12, J11.8, RN1.16
+5V: C2.1, C3.1, C4.1, C6.1, C8.1, C9.1, C10.1, C11.1, C201.1, C202.1, D1.1, D1.2, J7.14, J9.1, J10.14, J11.2, J11.4, J11.6, J12.1, L201.1, U1.14, U201.2, U201.3
+12V: C206.1, C207.1, D201.1, J201.2, R203.1
/12-Boost/COMP: C204.1, R202.2, U201.7
/12-Boost/FB: R203.2, R204.1, U201.8
/12-Boost/FET_DRV: J201.3, Q201.3
/12-Boost/FREQ: R201.1, U201.9
/12-Boost/SS: C203.1, U201.4
/12-Boost/SW: D201.2, L201.2, U201.1, U201.15, U201.16
/DIN: D1.4, TP1.1, U1.6
/DO: D1.3, J10.5
/IO0: J3.2, J8.3, RN1.12
/IO1: J3.3, J8.4, RN1.13
/IO2: J3.4, J8.5, RN1.14
/IO3: J3.5, J8.6, RN1.15
/IO4: J3.6, J8.8, RN1.2
/IO5: J3.7, J8.7, RN1.1
/IO6: J3.8, U1.2
/IO6_H: J10.4, U1.3
/IO7: J3.9, U1.5
/IO8: J3.10, U1.9
/IO8_H: J10.2, U1.8
/IO9: J3.11, U1.12
/IO9_H: J10.3, U1.11
/IO10: J3.12, J8.9, RN1.3
/IO11: J3.13, J8.10, RN1.4
/IO12: J3.14, J8.11, RN1.5
/IO14: J7.2, J8.12, RN1.6
/IO15: J7.3, J8.13, RN1.8
/IO16: J7.4, J8.14, RN1.7
/IO18: J7.6, J10.7
/IO19: J7.7, J10.8
/IO20: J7.8, J10.9
/IO21: J7.9, J10.10
/IO22: J7.10, J10.11
/IO23: J7.11, U1.1, U1.4, U1.10, U1.13
/Program: J5.4, SW1.1
FET_CTL: J7.5, J10.6, Q201.1, RN1.9
GND: C1.2, C2.2, C3.2, C4.2, C6.2, C8.2, C9.2, C10.2, C11.2, C12.2, C13.2, C14.2, C201.2, C202.2, C203.2, C204.2, C205.2, C206.2, C207.2, D1.5, D1.6, J3.1, J5.3, J7.13, J8.2, J10.1, J10.13, J11.1, J11.3, J11.5, J11.7, J12.2, J201.1, Q201.2, R201.2, R204.2, SW1.2, U1.7, U201.6, U201.11, U201.12, U201.13, U201.17
unnamed: C205.1, R202.1
unnamed: RN1.10, TP3.1
unnamed: RN1.11, TP2.1

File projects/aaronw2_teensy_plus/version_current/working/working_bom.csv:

"Id";"Designator";"Footprint";"Quantity";"Designation";"Supplier and ref";
1;"FID5,FID4,FID3,FID6,FID2,FID1";"Fiducial_0.5mm_Mask1mm";6;"FIDUCIAL_1MM";;;
2;"SW1";"SW_SPST_KMR2";1;"SW_SPST_KMR2";;;
3;"RN1";"R_Array_Convex_8x0602";1;"100K";;;
4;"J8";"PinHeader_2x07_P2.54mm_Vertical";1;"Conn_02x07_Odd_Even";;;
5;"C11,C9,C14,C10";"C_0805_2012Metric";4;"10uF";;;
6;"C8,C4,C1,C202,C13,C2";"C_0603_1608Metric";6;"0.1uF";;;
7;"C6,C207,C12,C3";"C_0603_1608Metric";4;"1uF";;;
8;"J201";"PinHeader_1x03_P2.54mm_Vertical";1;"Conn_01x03";;;
9;"U201";"QFN-16-1EP_3x3mm_P0.5mm_EP2.7x2.7mm_ThermalVias";1;"TPS55340-Q1";;;
10;"R204";"R_0603_1608Metric";1;"10k";;;
11;"R203";"R_0603_1608Metric";1;"86.6k";;;
12;"R202";"R_0603_1608Metric";1;"1.62k";;;
13;"R201";"R_0603_1608Metric";1;"18.7K";;;
14;"Q201";"SOT-323_SC-70";1;"BSS214NW";;;
15;"L201";"L_Vishay_IHLP-1212";1;"3.3uH";;;
16;"D201";"D_SOD-123F";1;"SS24FL";;;
17;"C206";"C_1210_3225Metric";1;"47uF";;;
18;"C205";"C_0603_1608Metric";1;"47nF";;;
19;"C204";"C_0603_1608Metric";1;"820pF";;;
20;"C203";"C_0603_1608Metric";1;"22nF";;;
21;"C201";"C_0603_1608Metric";1;"22uF";;;
22;"U1";"Texas_S-PVQFN-N14";1;"SN74AHCT125N";;;
23;"J11";"PinHeader_2x04_P2.54mm_Vertical";1;"Conn_02x04_Odd_Even";;;
24;"J12";"PinHeader_1x02_P2.54mm_Vertical";1;"Conn_01x02";;;
25;"D1";"LED_WS2813-MINI-2";1;"WS2813-MINI";;;
26;"J10";"PinHeader_1x14_P2.54mm_Vertical";1;"Conn_01x14";;;
27;"J7,J3";"PinHeader_1x14_P2.54mm_Vertical";2;"Conn_01x14_Male";;;
28;"J9";"PinHeader_1x01_P2.54mm_Vertical";1;"Conn_01x01_Male";;;
29;"J5";"PinHeader_1x05_P2.54mm_Vertical";1;"Conn_01x05_Male";;;

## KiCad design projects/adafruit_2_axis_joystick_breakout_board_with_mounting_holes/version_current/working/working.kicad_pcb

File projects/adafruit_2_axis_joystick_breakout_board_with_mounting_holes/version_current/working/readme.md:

# 2-axis-joystick-breakout-board-with-mounting-holes by adafruit  
This is a harvested standardized copy of a project from github.  
The original project can be found at:  
https://github.com/adafruit/2-axis-joystick-breakout-board-with-mounting-holes  
Please consult that link for additional, details, files, and license information.  
Note: It was auto harvested and if the original repo had more than one board file or anything out of the ordinary the files here are likely not representative.

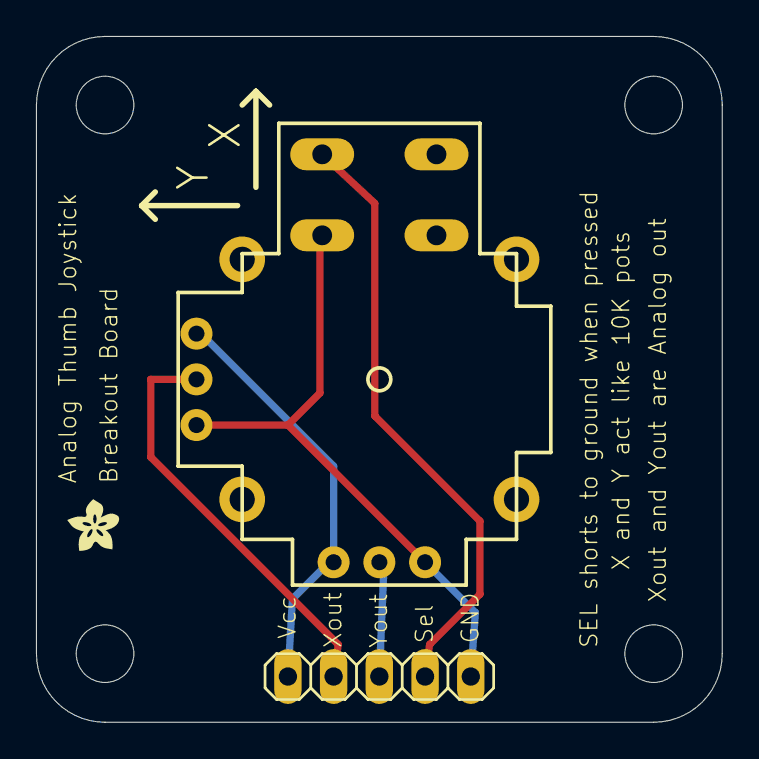
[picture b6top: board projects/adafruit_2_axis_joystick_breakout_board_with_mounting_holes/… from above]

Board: 16 copper layers, 38.1 x 38.1 mm, 7 parts (0 on the bottom side), 5 nets.

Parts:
@HOLE0, @HOLE1, @HOLE2, @HOLE3: (no value)
JP1: 1X05
U1: JOYSTICKPTH; JOYSTICK
U$1: ADAFRUIT200MIL

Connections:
unnamed: JP1.5, U1.H1, U1.V1
unnamed: JP1.1, U1.B2A, U1.H3, U1.V3
unnamed: JP1.4, U1.V2
unnamed: JP1.3, U1.H2
unnamed: JP1.2, U1.B1A

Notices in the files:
projects/aaronw2_el_driver_3/version_current/working/working.kicad_pcb:
Copyright © 2021 Aaron Williams
projects/aaronw2_led_controller_v4/version_current/working/working.kicad_pcb:
Copyright © 2020-2022 by Aaron Williams
Copyright ©
projects/aaronw2_led_controller_wrover32/version_current/working/working.kicad_pcb:
Copyright © 2019 by Aaron Williams
projects/aaronw2_slimevr/version_current/working/working.kicad_pcb:
Copyright © 2022 Aaron Williams
projects/aaronw2_teensy_plus/version_current/working/working.kicad_pcb:
Copyright (C) 2019 Aaron Williams
© 2020 by Aaron Williams
